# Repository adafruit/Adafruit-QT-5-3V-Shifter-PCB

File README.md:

## Adafruit QT 5-3V Shifter Breakout - STEMMA QT/Qwiic PCB

<a href="http://www.adafruit.com/products/5637"><br/>
Click here to purchase one from the Adafruit shop</a>

PCB files for the Adafruit QT 5-3V Shifter Breakout - STEMMA QT/Qwiic. 

Format is EagleCAD schematic and board layout
* https://www.adafruit.com/product/5637

### Description

If you're hankerin' to use the new Qwiic / Stemma QT standard for your next project - but you're still using a classic Arduino UNO or other 5V microcontroller, this board is designed for you! Note that Adafruit QT boards are all 3V and 5V safe but many other Qwiic and other I2C devices are not 5V safe or compatible. That means that if you use wires to connect a Qwiic board to a 5V microcontroller you risk damaging your shiny new I2C sensor with over-high voltages. Unless, of course you have one of these Adafruit QT 5V to 3V Shifter Breakouts

On one side is 5V-safe power and logic input. In the middle is a 3.3V regulator that can provide 500mA plus level shifting circuitry. On the opposite side is the same I2C traffic but now safely shifted down to 3.3V to allow usage with the vast number of sensors and devices that are not 5V safe.

It's simple but very effective! You also get breadboard breakout pins for breadboard usage so it can also be used as a QT-to-perfboard adapter.

The STEMMA QT connectors on either side are compatible with the  I2C connectors. This allows you to make solderless connections between your development board and the QT Shifter or to chain it with a wide range of other sensors and accessories using a compatible cable. QT Cable is not included, but we have a variety in the shop.

### License

Adafruit invests time and resources providing this open source design, please support Adafruit and open-source hardware by purchasing products from [Adafruit](https://www.adafruit.com)!

Designed by Limor Fried/Ladyada for Adafruit Industries.

Creative Commons Attribution/Share-Alike, all text above must be included in any redistribution. 
See license.txt for additional details.

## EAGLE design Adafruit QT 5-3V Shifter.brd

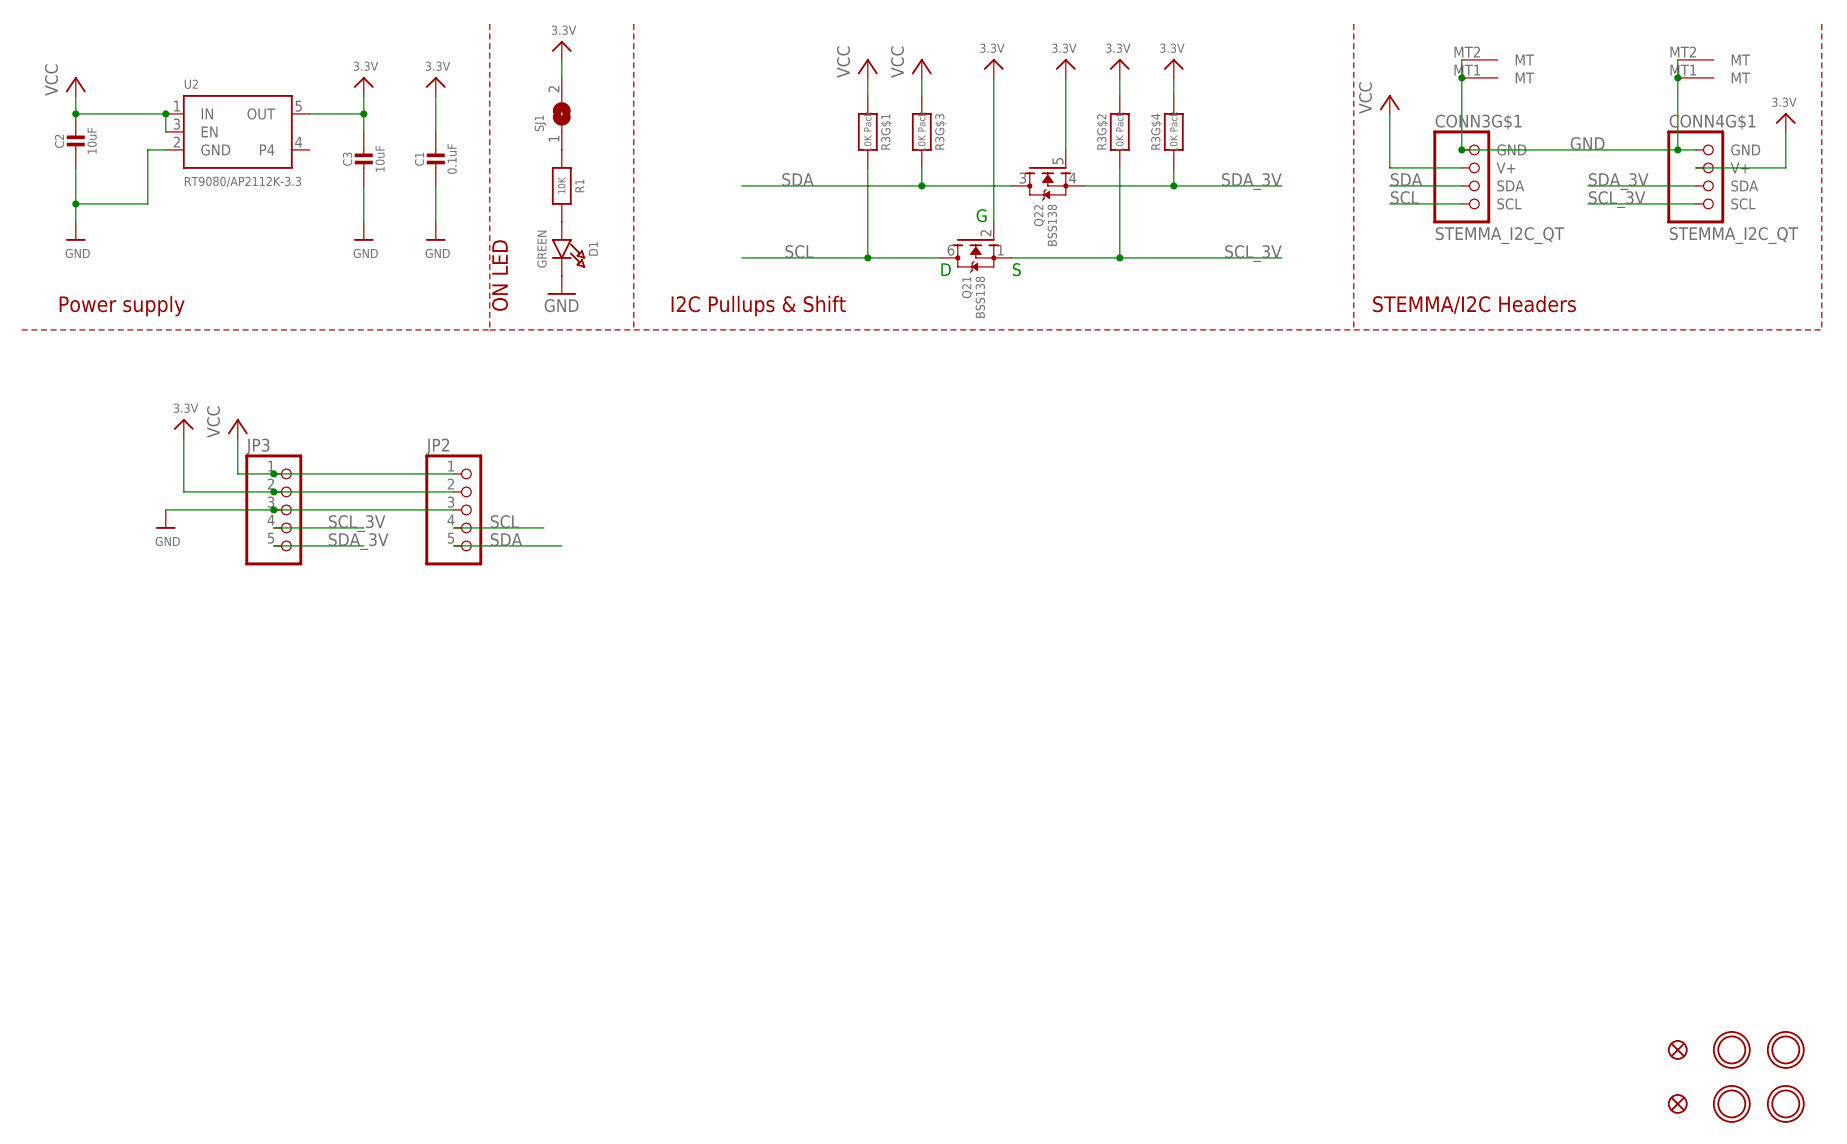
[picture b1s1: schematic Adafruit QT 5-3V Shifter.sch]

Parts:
C1: 0.1uF; 0603-NO
C2, C3: 10uF; 0805-NO
CONN3, CONN4: STEMMA_I2C_QT; JST_SH4
D1: GREEN; CHIPLED_0603_NOOUTLINE
FID3, FID4: FIDUCIAL_1MM
JP2, JP3: HEADER-1X576MIL; 1X05_ROUND_76
Q2: BSS138; SOT363
R1: 10K; 0603-NO
R3: 10K Pack; RESPACK_4X0603
SJ1: SOLDERJUMPERCLOSED; SOLDERJUMPER_CLOSEDWIRE
U2: RT9080/AP2112K-3.3; SOT23-5; JLC_ROTATION 0
U$1, U$17, U$19, U$21: MOUNTINGHOLE2.5; MOUNTINGHOLE_2.5_PLATED

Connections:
3.3V: C1.1, C3.1, CONN4.2 (V+), JP2.2, JP3.2, Q2.2 (G), Q2.5 (G), R3.2 (1), R3.4 (1), SJ1.2, U2.5 (OUT)
GND: C1.2, C2.2, C3.2, CONN3.1 (GND), CONN3.MT1 (MT), CONN3.MT2 (MT), CONN4.1 (GND), CONN4.MT1 (MT), CONN4.MT2 (MT), D1.C, JP2.3, JP3.3, U2.2 (GND)
unnamed: D1.A, R1.2
unnamed: R1.1, SJ1.1
SCL: CONN3.4 (SCL), JP2.4, Q2.6 (D), R3.8 (2)
SCL_3V: CONN4.4 (SCL), JP3.4, Q2.1 (S), R3.7 (2)
SDA: CONN3.3 (SDA), JP2.5, Q2.3 (D), R3.6 (2)
SDA_3V: CONN4.3 (SDA), JP3.5, Q2.4 (S), R3.5 (2)
VCC: C2.1, CONN3.2 (V+), JP2.1, JP3.1, R3.1, R3.3 (1), U2.1 (IN), U2.3 (EN)

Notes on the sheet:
I2C Pullups & Shift
STEMMA/I2C Headers
ON LED
Power supply

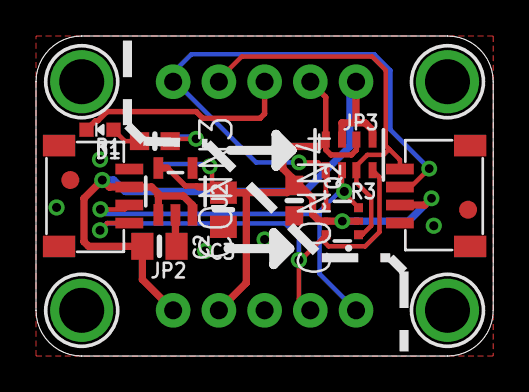
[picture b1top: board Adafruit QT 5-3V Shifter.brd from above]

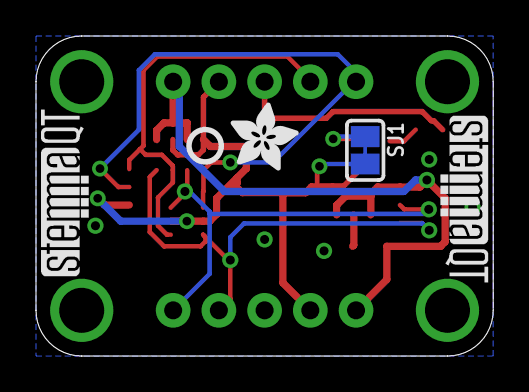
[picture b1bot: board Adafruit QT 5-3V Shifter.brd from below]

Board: 2 copper layers, 25.4 x 17.8 mm, 38 parts (7 on the bottom side), 9 nets.

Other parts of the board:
PLABEL0: PLABEL0
PLABEL1: PLABEL1
PLABEL2: PLABEL2
PLABEL3: PLABEL3
PLABEL4: PLABEL4
PLABEL5: PLABEL5
PLABEL6: PLABEL6
PLABEL7: PLABEL7
PLABEL8: PLABEL8
PLABEL9: PLABEL9
PLABEL10: PLABEL10
PLABEL11: PLABEL11
PLABEL12: PLABEL12
PLABEL13: PLABEL13
PLABEL14: PLABEL14
U$2: ADAFRUIT_3.5MM
U$25: PCBFEAT-REV-040
U$30, U$31: STEMMAQT

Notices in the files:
parts and their libraries:
microbuilder: This work is placed in the public domain, and may be freely used for commercial and non-commercial work with the following conditions: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
